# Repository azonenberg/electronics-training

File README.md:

Open source classes on electrical engineering and electronic hardware design

Each class is intended to be approximately a half day when offered consecutively in a conference/workshop format: 3
hours of lecture and 2 hour of lab.

# Current focus

* Oscilloscope probing, including detailed discussions of probe architectures and non-idealities

# Future ideas (may be more than one class each)

* Electronics merit badge
* EE 101
* PCB design
* High speed design
* EM simulation with Sonnet(?)

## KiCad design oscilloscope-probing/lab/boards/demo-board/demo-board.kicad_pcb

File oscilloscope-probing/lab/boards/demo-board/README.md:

# Demo board

## info

* ebay xc7a35t-2fgg484i
* stm32h750 running control plane
* 4x LVCMOS33 outputs for low speed stuff, wired direct from FPGA to SMAs
* A few GTPs to SMAs
* ltc3374a based power, usb-c, f234
* Some fast LVCMOS18 or similar outputs
* needs 32 mbit or larger spi flash, load more fw for stm32 from same flash if needed??

stackup: 8 layers SGS PG SGS JLC081611-2116?? going down to 6 probably wont save much

## BUGS BUGS BUGS in first board revision

* FT234 is 0.45mm pitch, footprint is 0.5. it should still solder, barely (150um max pin position error, 250um lands w/ 250um gaps)
* No pulldowns on rail enables, so they all turn on without sequencing until the supervisor is flashed and out of reset
* Not really a bug, but should have put DC blocks on PAM3 outputs so we don't need them scope side
* LTC3374A MODE pin is strapped low which causes high ripple on GTY VTT (1.2V) rail due to light load, should have been high
* Add lowpass filter to PAM3 outputs to simulate ethernet magnetics response
* Missing solder paste apertures on USB connector mechanical pins and several PTH headers that could otherwise have been pin-in-paste soldered

NOTE NOTE NOTE
Board 3 C122 has 10uf instead of 22

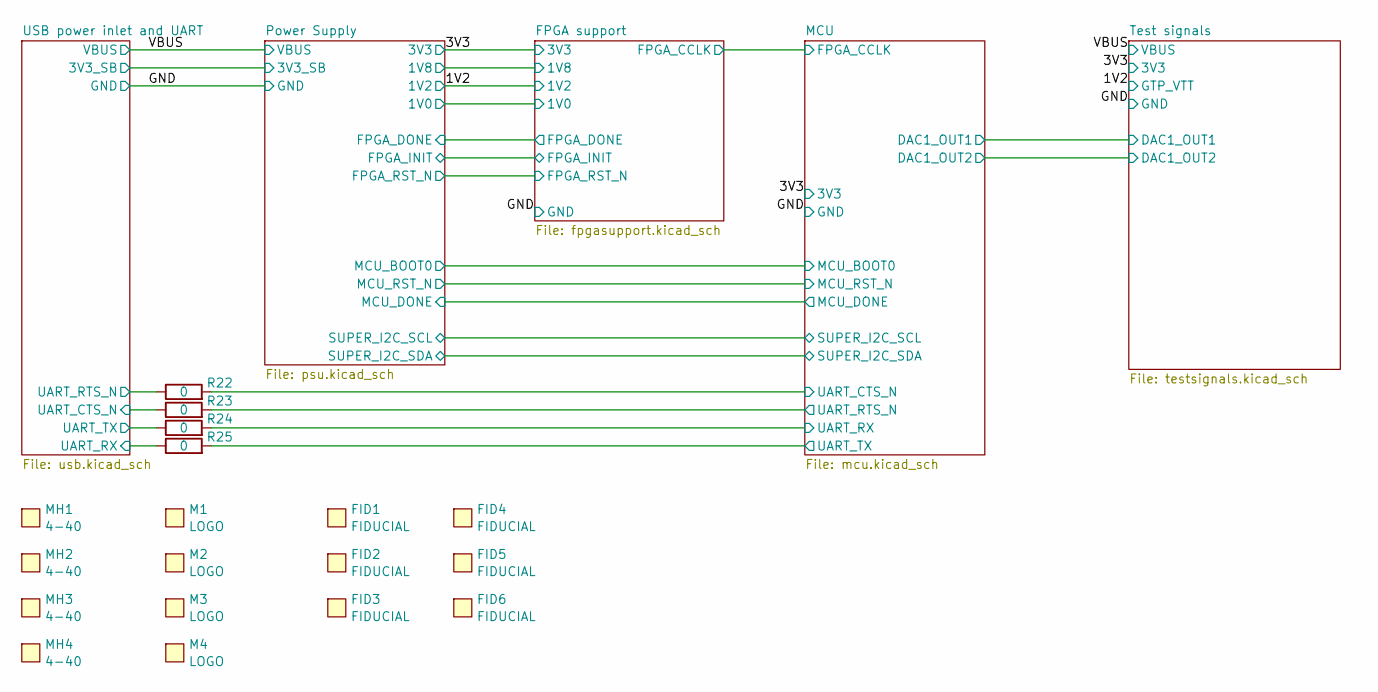
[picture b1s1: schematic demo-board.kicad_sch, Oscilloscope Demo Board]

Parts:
FID1, FID2, FID3, FID4, FID5, FID6: FIDUCIAL; FIDUCIAL_1MM
M1: LOGO; LONGTHING-1200DPI
M2: LOGO; Logo_silk_ROHS_5x2.8mm
M3: LOGO; Logo_silk_WEEE_3.4x5mm
M4: LOGO; Logo_silk_OSHW_6x6mm
MH1, MH2, MH3, MH4: 4-40; MECHANICAL_CLEARANCEHOLE_4_40
R22, R23, R24, R25: 0; EIA_0402_RES_NOSILK

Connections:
/MCU/UART_CTS_N: R22.2; also elsewhere on the board
/MCU/UART_RTS_N: R23.2; also elsewhere on the board
/MCU/UART_RX: R24.2; also elsewhere on the board
/MCU/UART_TX: R25.2; also elsewhere on the board
/USB power inlet and UART/UART_CTS_N: R23.1; also elsewhere on the board
/USB power inlet and UART/UART_RTS_N: R22.1; also elsewhere on the board
/USB power inlet and UART/UART_RX: R25.1; also elsewhere on the board
/USB power inlet and UART/UART_TX: R24.1; also elsewhere on the board

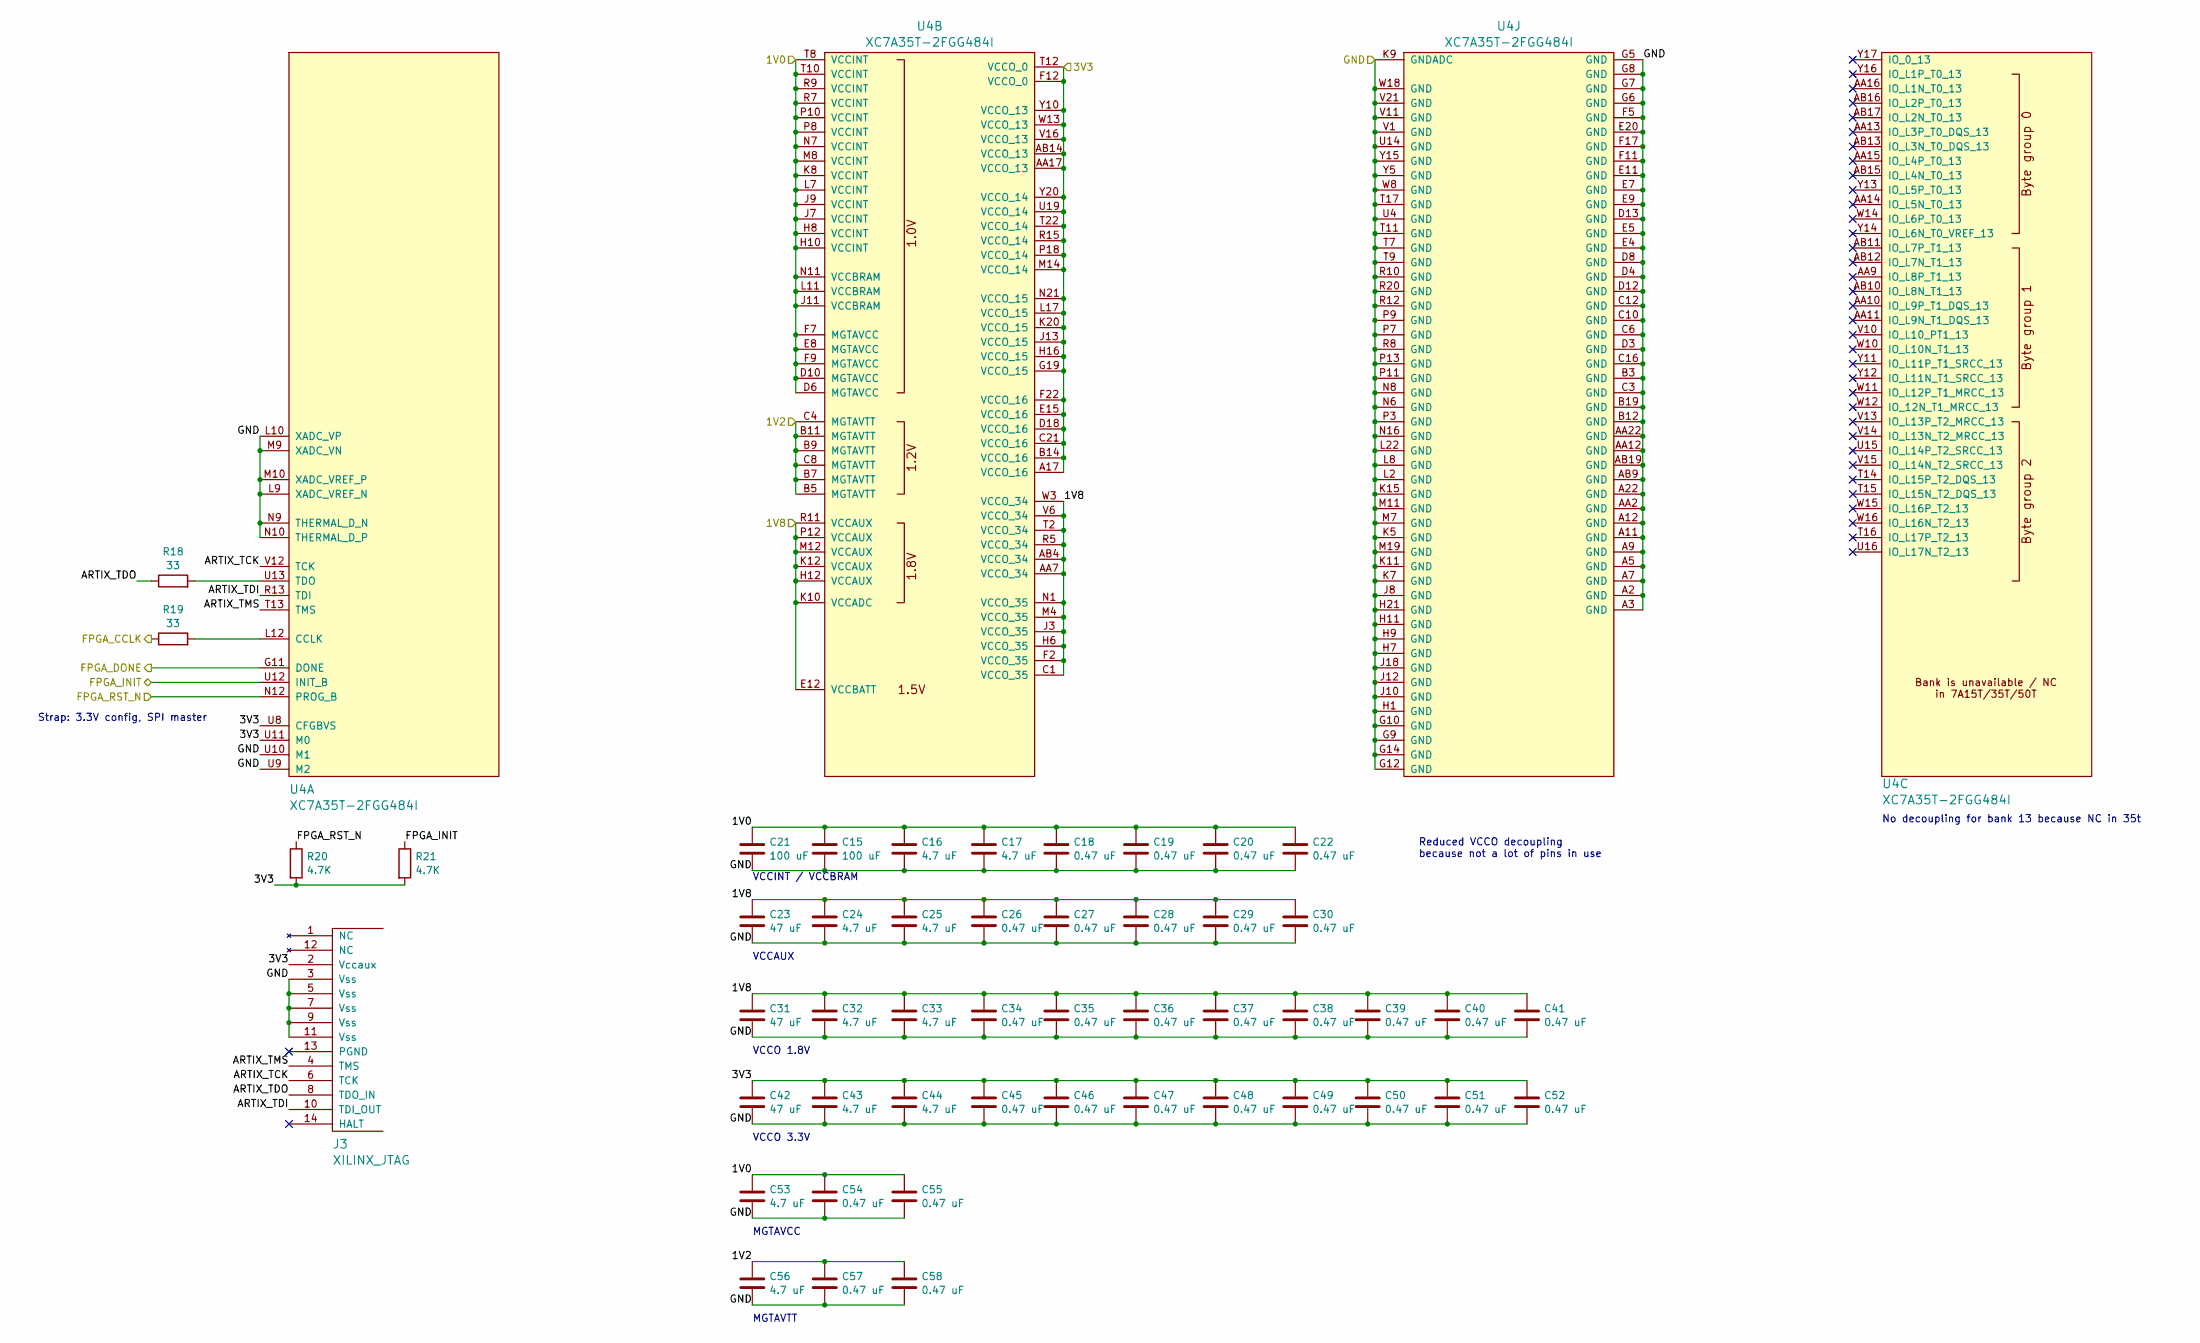
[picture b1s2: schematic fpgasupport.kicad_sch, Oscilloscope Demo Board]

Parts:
C15, C21: 100 uF; EIA_1206_CAP_NOSILK
C16, C17, C24, C25, C32, C33, C43, C44, C53, C56: 4.7 uF; EIA_0603_CAP_NOSILK
C18, C19, C20, C22, C26, C27, C28, C29, C30, C34, C35, C36, C37, C38, C39, C40, C41, C45, C46, C47, C48, C49, C50, C51, C52, C54, C55, C57, C58: 0.47 uF; EIA_0402_CAP_NOSILK
C23, C31, C42: 47 uF; EIA_1206_CAP_NOSILK
J3: XILINX_JTAG; XILINX_JTAG_PTH_MOLEX_0878311420
R18, R19: 33; EIA_0402_RES_NOSILK
R20, R21: 4.7K; EIA_0402_RES_NOSILK
U4: XC7A35T-2FGG484I; BGA_484_22x22_FULLARRAY_1MM

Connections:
/1V2: C56.1, C57.1, C58.1, U4.B5 (MGTAVTT), U4.B7 (MGTAVTT), U4.B9 (MGTAVTT), U4.B11 (MGTAVTT), U4.C4 (MGTAVTT), U4.C8 (MGTAVTT); also elsewhere on the board
/3V3: C42.1, C43.1, C44.1, C45.1, C46.1, C47.1, C48.1, C49.1, C50.1, C51.1, C52.1, J3.2 (Vccaux), R20.2, R21.2, U4.A17 (VCCO_16), U4.AA17 (VCCO_13), U4.AB14 (VCCO_13), U4.B14 (VCCO_16), U4.C21 (VCCO_16), U4.D18 (VCCO_16), U4.E15 (VCCO_16), U4.F12 (VCCO_0), U4.F22 (VCCO_16), U4.G19 (VCCO_15), U4.H16 (VCCO_15), U4.J13 (VCCO_15), U4.K20 (VCCO_15), U4.L17 (VCCO_15), U4.M14 (VCCO_14), U4.N21 (VCCO_15), U4.P18 (VCCO_14), U4.R15 (VCCO_14), U4.T12 (VCCO_0), U4.T22 (VCCO_14), U4.U8 (CFGBVS), U4.U11 (M0), U4.U19 (VCCO_14), U4.V16 (VCCO_13), U4.W13 (VCCO_13), U4.Y10 (VCCO_13), U4.Y20 (VCCO_14); also elsewhere on the board
/FPGA support/1V0: C15.1, C16.1, C17.1, C18.1, C19.1, C20.1, C21.1, C22.1, C53.1, C54.1, C55.1, U4.D6 (MGTAVCC), U4.D10 (MGTAVCC), U4.E8 (MGTAVCC), U4.F7 (MGTAVCC), U4.F9 (MGTAVCC), U4.H8 (VCCINT), U4.H10 (VCCINT), U4.J7 (VCCINT), U4.J9 (VCCINT), U4.J11 (VCCBRAM), U4.K8 (VCCINT), U4.L7 (VCCINT), U4.L11 (VCCBRAM), U4.M8 (VCCINT), U4.N7 (VCCINT), U4.N11 (VCCBRAM), U4.P8 (VCCINT), U4.P10 (VCCINT), U4.R7 (VCCINT), U4.R9 (VCCINT), U4.T8 (VCCINT), U4.T10 (VCCINT); also elsewhere on the board
/FPGA support/1V8: C23.1, C24.1, C25.1, C26.1, C27.1, C28.1, C29.1, C30.1, C31.1, C32.1, C33.1, C34.1, C35.1, C36.1, C37.1, C38.1, C39.1, C40.1, C41.1, U4.AA7 (VCCO_34), U4.AB4 (VCCO_34), U4.C1 (VCCO_35), U4.E12 (VCCBATT), U4.F2 (VCCO_35), U4.H6 (VCCO_35), U4.H12 (VCCAUX), U4.J3 (VCCO_35), U4.K10 (VCCADC), U4.K12 (VCCAUX), U4.M4 (VCCO_35), U4.M12 (VCCAUX), U4.N1 (VCCO_35), U4.P12 (VCCAUX), U4.R5 (VCCO_34), U4.R11 (VCCAUX), U4.T2 (VCCO_34), U4.V6 (VCCO_34), U4.W3 (VCCO_34); also elsewhere on the board
/FPGA support/ARTIX_TCK: J3.6 (TCK), U4.V12 (TCK)
/FPGA support/ARTIX_TDI: J3.10 (TDI_OUT), U4.R13 (TDI)
/FPGA support/ARTIX_TDO: J3.8 (TDO_IN), R18.1
/FPGA support/ARTIX_TMS: J3.4 (TMS), U4.T13 (TMS)
/FPGA support/FPGA_CCLK: R19.1; also elsewhere on the board
/FPGA support/FPGA_DONE: U4.G11 (DONE); also elsewhere on the board
/FPGA support/FPGA_INIT: R21.1, U4.U12 (INIT_B); also elsewhere on the board
/FPGA support/FPGA_RST_N: R20.1, U4.N12 (PROG_B); also elsewhere on the board
/GND: C15.2, C16.2, C17.2, C18.2, C19.2, C20.2, C21.2, C22.2, C23.2, C24.2, C25.2, C26.2, C27.2, C28.2, C29.2, C30.2, C31.2, C32.2, C33.2, C34.2, C35.2, C36.2, C37.2, C38.2, C39.2, C40.2, C41.2, C42.2, C43.2, C44.2, C45.2, C46.2, C47.2, C48.2, C49.2, C50.2, C51.2, C52.2, C53.2, C54.2, C55.2, C56.2, C57.2, C58.2, J3.3 (Vss), J3.5 (Vss), J3.7 (Vss), J3.9 (Vss), J3.11 (Vss), U4.A2 (GND), U4.A3 (GND), U4.A5 (GND), U4.A7 (GND), U4.A9 (GND), U4.A11 (GND), U4.A12 (GND), U4.A22 (GND), U4.AA2 (GND), U4.AA12 (GND), U4.AA22 (GND), U4.AB9 (GND), U4.AB19 (GND), U4.B3 (GND), U4.B12 (GND), U4.B19 (GND), U4.C3 (GND), U4.C6 (GND), U4.C10 (GND), U4.C12 (GND), U4.C16 (GND), U4.D3 (GND), U4.D4 (GND), U4.D8 (GND), U4.D12 (GND), U4.D13 (GND), U4.E4 (GND), U4.E5 (GND), U4.E7 (GND), U4.E9 (GND), U4.E11 (GND), U4.E20 (GND), U4.F5 (GND), U4.F11 (GND), U4.F17 (GND), U4.G5 (GND), U4.G6 (GND), U4.G7 (GND), U4.G8 (GND), U4.G9 (GND), U4.G10 (GND), U4.G12 (GND), U4.G14 (GND), U4.H1 (GND), U4.H7 (GND), U4.H9 (GND), U4.H11 (GND), U4.H21 (GND), U4.J8 (GND), U4.J10 (GND), U4.J12 (GND), U4.J18 (GND), U4.K5 (GND), U4.K7 (GND), U4.K9 (GNDADC), U4.K11 (GND), U4.K15 (GND), U4.L2 (GND), U4.L8 (GND), U4.L9 (XADC_VREF_N), U4.L10 (XADC_VP), U4.L22 (GND), U4.M7 (GND), U4.M9 (XADC_VN), U4.M10 (XADC_VREF_P), U4.M11 (GND), U4.M19 (GND), U4.N6 (GND), U4.N8 (GND), U4.N9 (THERMAL_D_N), U4.N10 (THERMAL_D_P), U4.N16 (GND), U4.P3 (GND), U4.P7 (GND), U4.P9 (GND), U4.P11 (GND), U4.P13 (GND), U4.R8 (GND), U4.R10 (GND), U4.R12 (GND), U4.R20 (GND), U4.T7 (GND), U4.T9 (GND), U4.T11 (GND), U4.T17 (GND), U4.U4 (GND), U4.U9 (M2), U4.U10 (M1), U4.U14 (GND), U4.V1 (GND), U4.V11 (GND), U4.V21 (GND), U4.W8 (GND), U4.W18 (GND), U4.Y5 (GND), U4.Y15 (GND); also elsewhere on the board
unnamed: R19.2, U4.L12 (CCLK)
unnamed: R18.2, U4.U13 (TDO)

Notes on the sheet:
VCCO 1.8V
VCCINT / VCCBRAM
MGTAVCC
Reduced VCCO decoupling because not a lot of pins in use
Strap: 3.3V config, SPI master
MGTAVTT
No decoupling for bank 13 because NC in 35t
VCCAUX
VCCO 3.3V

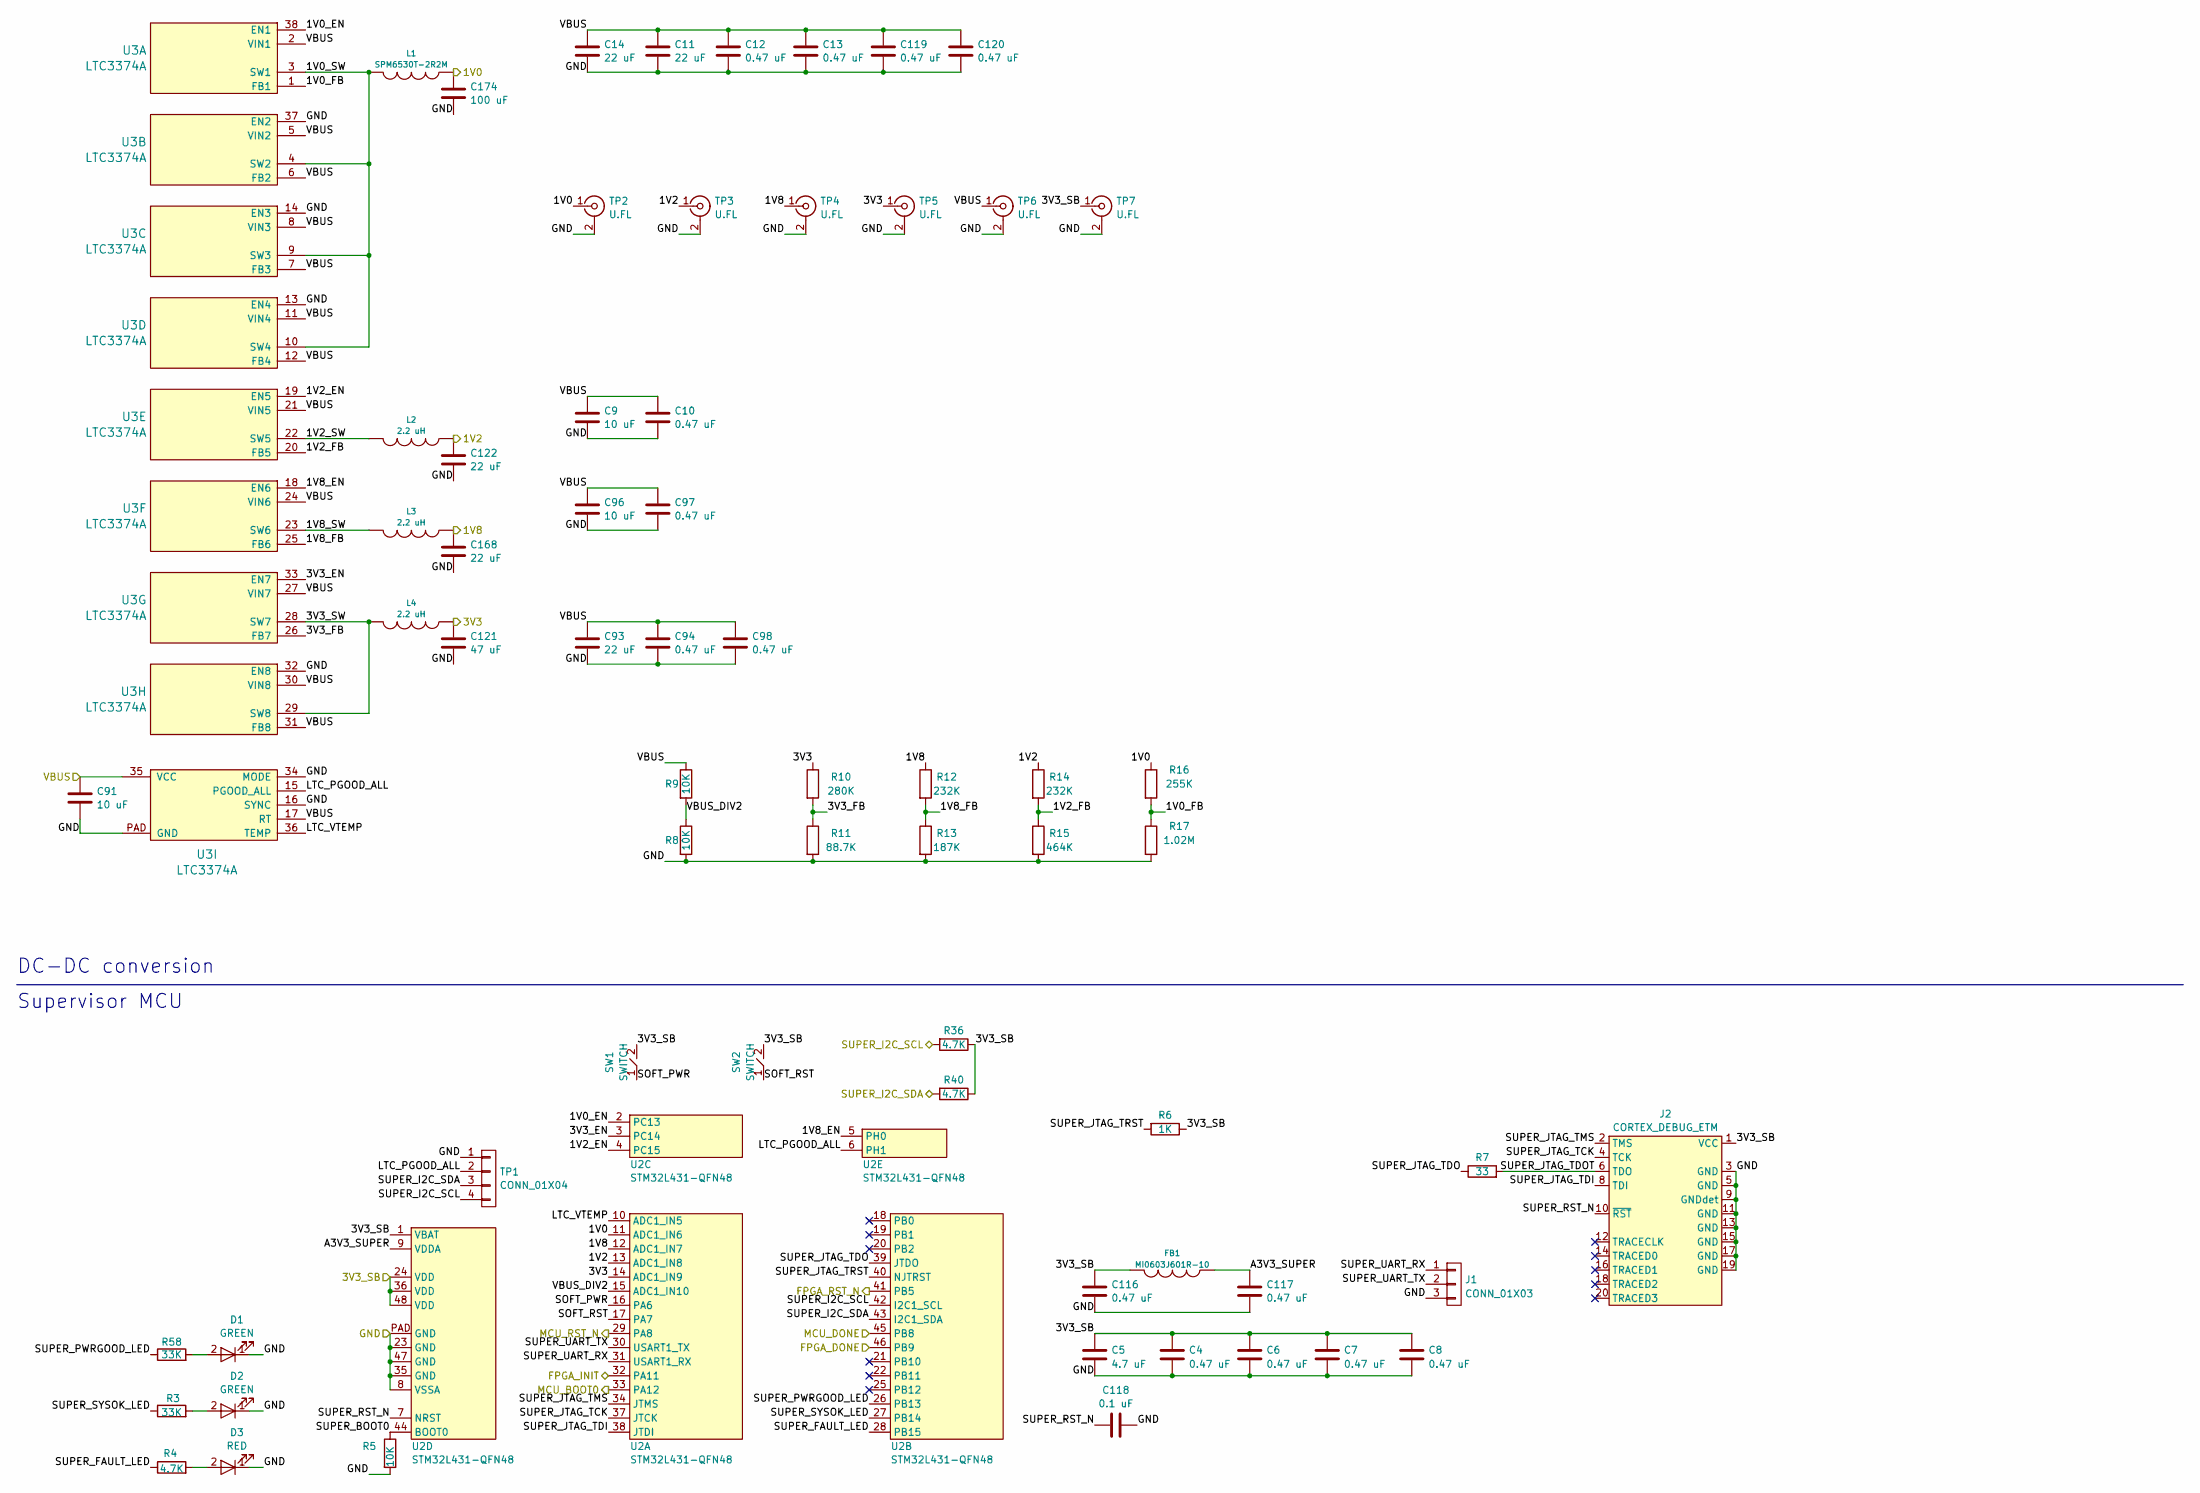
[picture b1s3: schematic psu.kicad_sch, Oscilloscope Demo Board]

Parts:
C4, C6, C7, C8, C10, C12, C13, C94, C97, C98, C116, C117, C119, C120: 0.47 uF; EIA_0402_CAP_NOSILK
C5: 4.7 uF; EIA_0603_CAP_NOSILK
C9, C91, C96: 10 uF; EIA_1210_CAP_NOSILK
C11, C14, C93: 22 uF; EIA_1210_CAP_NOSILK
C118: 0.1 uF; EIA_0402_CAP_NOSILK
C121: 47 uF; EIA_1210_CAP_NOSILK
C122, C168: 22 uF; EIA_0805_CAP_NOSILK
C174: 100 uF; EIA_1210_CAP_NOSILK
D1, D2: GREEN; EIA_0402_LED
D3: RED; EIA_0402_LED
FB1: MI0603J601R-10; EIA_0603_INDUCTOR_NOSILK
J1: CONN_01X03; CONN_HEADER_2.54MM_1x3
J2: CORTEX_DEBUG_ETM; CONN_HEADER_1.27MM_2x10_SMT_SAMTEC_FTSH-110-01-L-DV-K
L1: SPM6530T-2R2M; INDUCTOR_TDK_SPM6530
L2, L3, L4: 2.2 uH; EIA_1210_CAP_NOSILK
R3, R58: 33K; EIA_0402_RES_NOSILK
R4, R36, R40: 4.7K; EIA_0402_RES_NOSILK
R5, R8, R9: 10K; EIA_0402_RES_NOSILK
R6: 1K; EIA_0402_RES_NOSILK
R7: 33; EIA_0402_RES_NOSILK
R10: 280K; EIA_0402_RES_NOSILK
R11: 88.7K; EIA_0402_RES_NOSILK
R12, R14: 232K; EIA_0402_RES_NOSILK
R13: 187K; EIA_0402_RES_NOSILK
R15: 464K; EIA_0402_RES_NOSILK
R16: 255K; EIA_0402_RES_NOSILK
R17: 1.02M; EIA_0402_RES_NOSILK
SW1, SW2: SWITCH; SWITCH_RAFI_MICON_5
TP1: CONN_01X04; CONN_HEADER_2.54MM_1x4
TP2, TP3, TP4, TP5, TP6, TP7: U.FL; CONN_U.FL_TE_1909763-1
U2: STM32L431-QFN48; QFN_48_0.5MM_7x7MM
U3: LTC3374A; QFN_38_0.5MM_5x7MM

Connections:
/1V2: C122.1, L2.1, R14.1, TP3.1 (In), U2.13 (ADC1_IN8); also elsewhere on the board
/3V3: C121.1, L4.1, R10.1, TP5.1 (In), U2.14 (ADC1_IN9); also elsewhere on the board
/FPGA support/1V0: C174.1, L1.1, R16.1, TP2.1 (In), U2.11 (ADC1_IN6); also elsewhere on the board
/FPGA support/1V8: C168.1, L3.1, R12.1, TP4.1 (In), U2.12 (ADC1_IN7); also elsewhere on the board
/FPGA support/FPGA_DONE: U2.46 (PB9); also elsewhere on the board
/FPGA support/FPGA_INIT: U2.32 (PA11); also elsewhere on the board
/FPGA support/FPGA_RST_N: U2.41 (PB5); also elsewhere on the board
/GND: C4.2, C5.2, C6.2, C7.2, C8.2, C9.2, C10.2, C11.2, C12.2, C13.2, C14.2, C91.2, C93.2, C94.2, C96.2, C97.2, C98.2, C116.2, C117.2, C118.2, C119.2, C120.2, C121.2, C122.2, C168.2, C174.2, D1.1 (K), D2.1 (K), D3.1 (K), J1.3, J2.3 (GND), J2.5 (GND), J2.9 (GNDdet), J2.11 (GND), J2.13 (GND), J2.15 (GND), J2.17 (GND), J2.19 (GND), R5.2, R8.2, R11.2, R13.2, R15.2, R17.2, TP1.1, TP2.2 (Ext), TP3.2 (Ext), TP4.2 (Ext), TP5.2 (Ext), TP6.2 (Ext), TP7.2 (Ext), U2.8 (VSSA), U2.23 (GND), U2.35 (GND), U2.47 (GND), U2.PAD (GND), U3.13 (EN4), U3.14 (EN3), U3.16 (SYNC), U3.32 (EN8), U3.34 (MODE), U3.37 (EN2), U3.PAD (GND); also elsewhere on the board
/MCU/MCU_BOOT0: U2.33 (PA12); also elsewhere on the board
/MCU/MCU_DONE: U2.45 (PB8); also elsewhere on the board
/MCU/MCU_RST_N: U2.29 (PA8); also elsewhere on the board
/Power Supply/1V0_EN: U2.2 (PC13), U3.38 (EN1)
/Power Supply/1V0_FB: R16.2, R17.1, U3.1 (FB1)
/Power Supply/1V0_SW: L1.2, U3.3 (SW1), U3.4 (SW2), U3.9 (SW3), U3.10 (SW4)
/Power Supply/1V2_EN: U2.4 (PC15), U3.19 (EN5)
/Power Supply/1V2_FB: R14.2, R15.1, U3.20 (FB5)
/Power Supply/1V2_SW: L2.2, U3.22 (SW5)
/Power Supply/1V8_EN: U2.5 (PH0), U3.18 (EN6)
/Power Supply/1V8_FB: R12.2, R13.1, U3.25 (FB6)
/Power Supply/1V8_SW: L3.2, U3.23 (SW6)
/Power Supply/3V3_EN: U2.3 (PC14), U3.33 (EN7)
/Power Supply/3V3_FB: R10.2, R11.1, U3.26 (FB7)
/Power Supply/3V3_SB: C4.1, C5.1, C6.1, C7.1, C8.1, C116.1, FB1.2, J2.1 (VCC), R6.1, R36.1, R40.1, SW1.2, SW2.2, TP7.1 (In), U2.1 (VBAT), U2.24 (VDD), U2.36 (VDD), U2.48 (VDD); also elsewhere on the board
/Power Supply/3V3_SW: L4.2, U3.28 (SW7), U3.29 (SW8)
/Power Supply/A3V3_SUPER: C117.1, FB1.1, U2.9 (VDDA)
/Power Supply/LTC_PGOOD_ALL: TP1.2, U2.6 (PH1), U3.15 (PGOOD_ALL)
/Power Supply/LTC_VTEMP: U2.10 (ADC1_IN5), U3.36 (TEMP)
/Power Supply/SOFT_PWR: SW1.1, U2.16 (PA6)
/Power Supply/SOFT_RST: SW2.1, U2.17 (PA7)
/Power Supply/SUPER_BOOT0: R5.1, U2.44 (BOOT0)
/Power Supply/SUPER_FAULT_LED: R4.1, U2.28 (PB15)
/Power Supply/SUPER_I2C_SCL: R36.2, TP1.4, U2.42 (I2C1_SCL); also elsewhere on the board
/Power Supply/SUPER_I2C_SDA: R40.2, TP1.3, U2.43 (I2C1_SDA); also elsewhere on the board
/Power Supply/SUPER_JTAG_TCK: J2.4 (TCK), U2.37 (JTCK)
/Power Supply/SUPER_JTAG_TDI: J2.8 (TDI), U2.38 (JTDI)
/Power Supply/SUPER_JTAG_TDO: R7.1, U2.39 (JTDO)
/Power Supply/SUPER_JTAG_TDOT: J2.6 (TDO), R7.2
/Power Supply/SUPER_JTAG_TMS: J2.2 (TMS), U2.34 (JTMS)
/Power Supply/SUPER_JTAG_TRST: R6.2, U2.40 (NJTRST)
/Power Supply/SUPER_PWRGOOD_LED: R58.1, U2.26 (PB13)
/Power Supply/SUPER_RST_N: C118.1, J2.10 (~RST), U2.7 (NRST)
/Power Supply/SUPER_SYSOK_LED: R3.1, U2.27 (PB14)
/Power Supply/SUPER_UART_RX: J1.1, U2.31 (USART1_RX)
/Power Supply/SUPER_UART_TX: J1.2, U2.30 (USART1_TX)
/Power Supply/VBUS_DIV2: R8.1, R9.2, U2.15 (ADC1_IN10)
/VBUS: C9.1, C10.1, C11.1, C12.1, C13.1, C14.1, C91.1, C93.1, C94.1, C96.1, C97.1, C98.1, C119.1, C120.1, R9.1, TP6.1 (In), U3.2 (VIN1), U3.5 (VIN2), U3.6 (FB2), U3.7 (FB3), U3.8 (VIN3), U3.11 (VIN4), U3.12 (FB4), U3.17 (RT), U3.21 (VIN5), U3.24 (VIN6), U3.27 (VIN7), U3.30 (VIN8), U3.31 (FB8), U3.35 (VCC); also elsewhere on the board
unnamed: D1.2 (A), R58.2
unnamed: D2.2 (A), R3.2
unnamed: D3.2 (A), R4.2

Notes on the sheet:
DC-DC conversion
Supervisor MCU

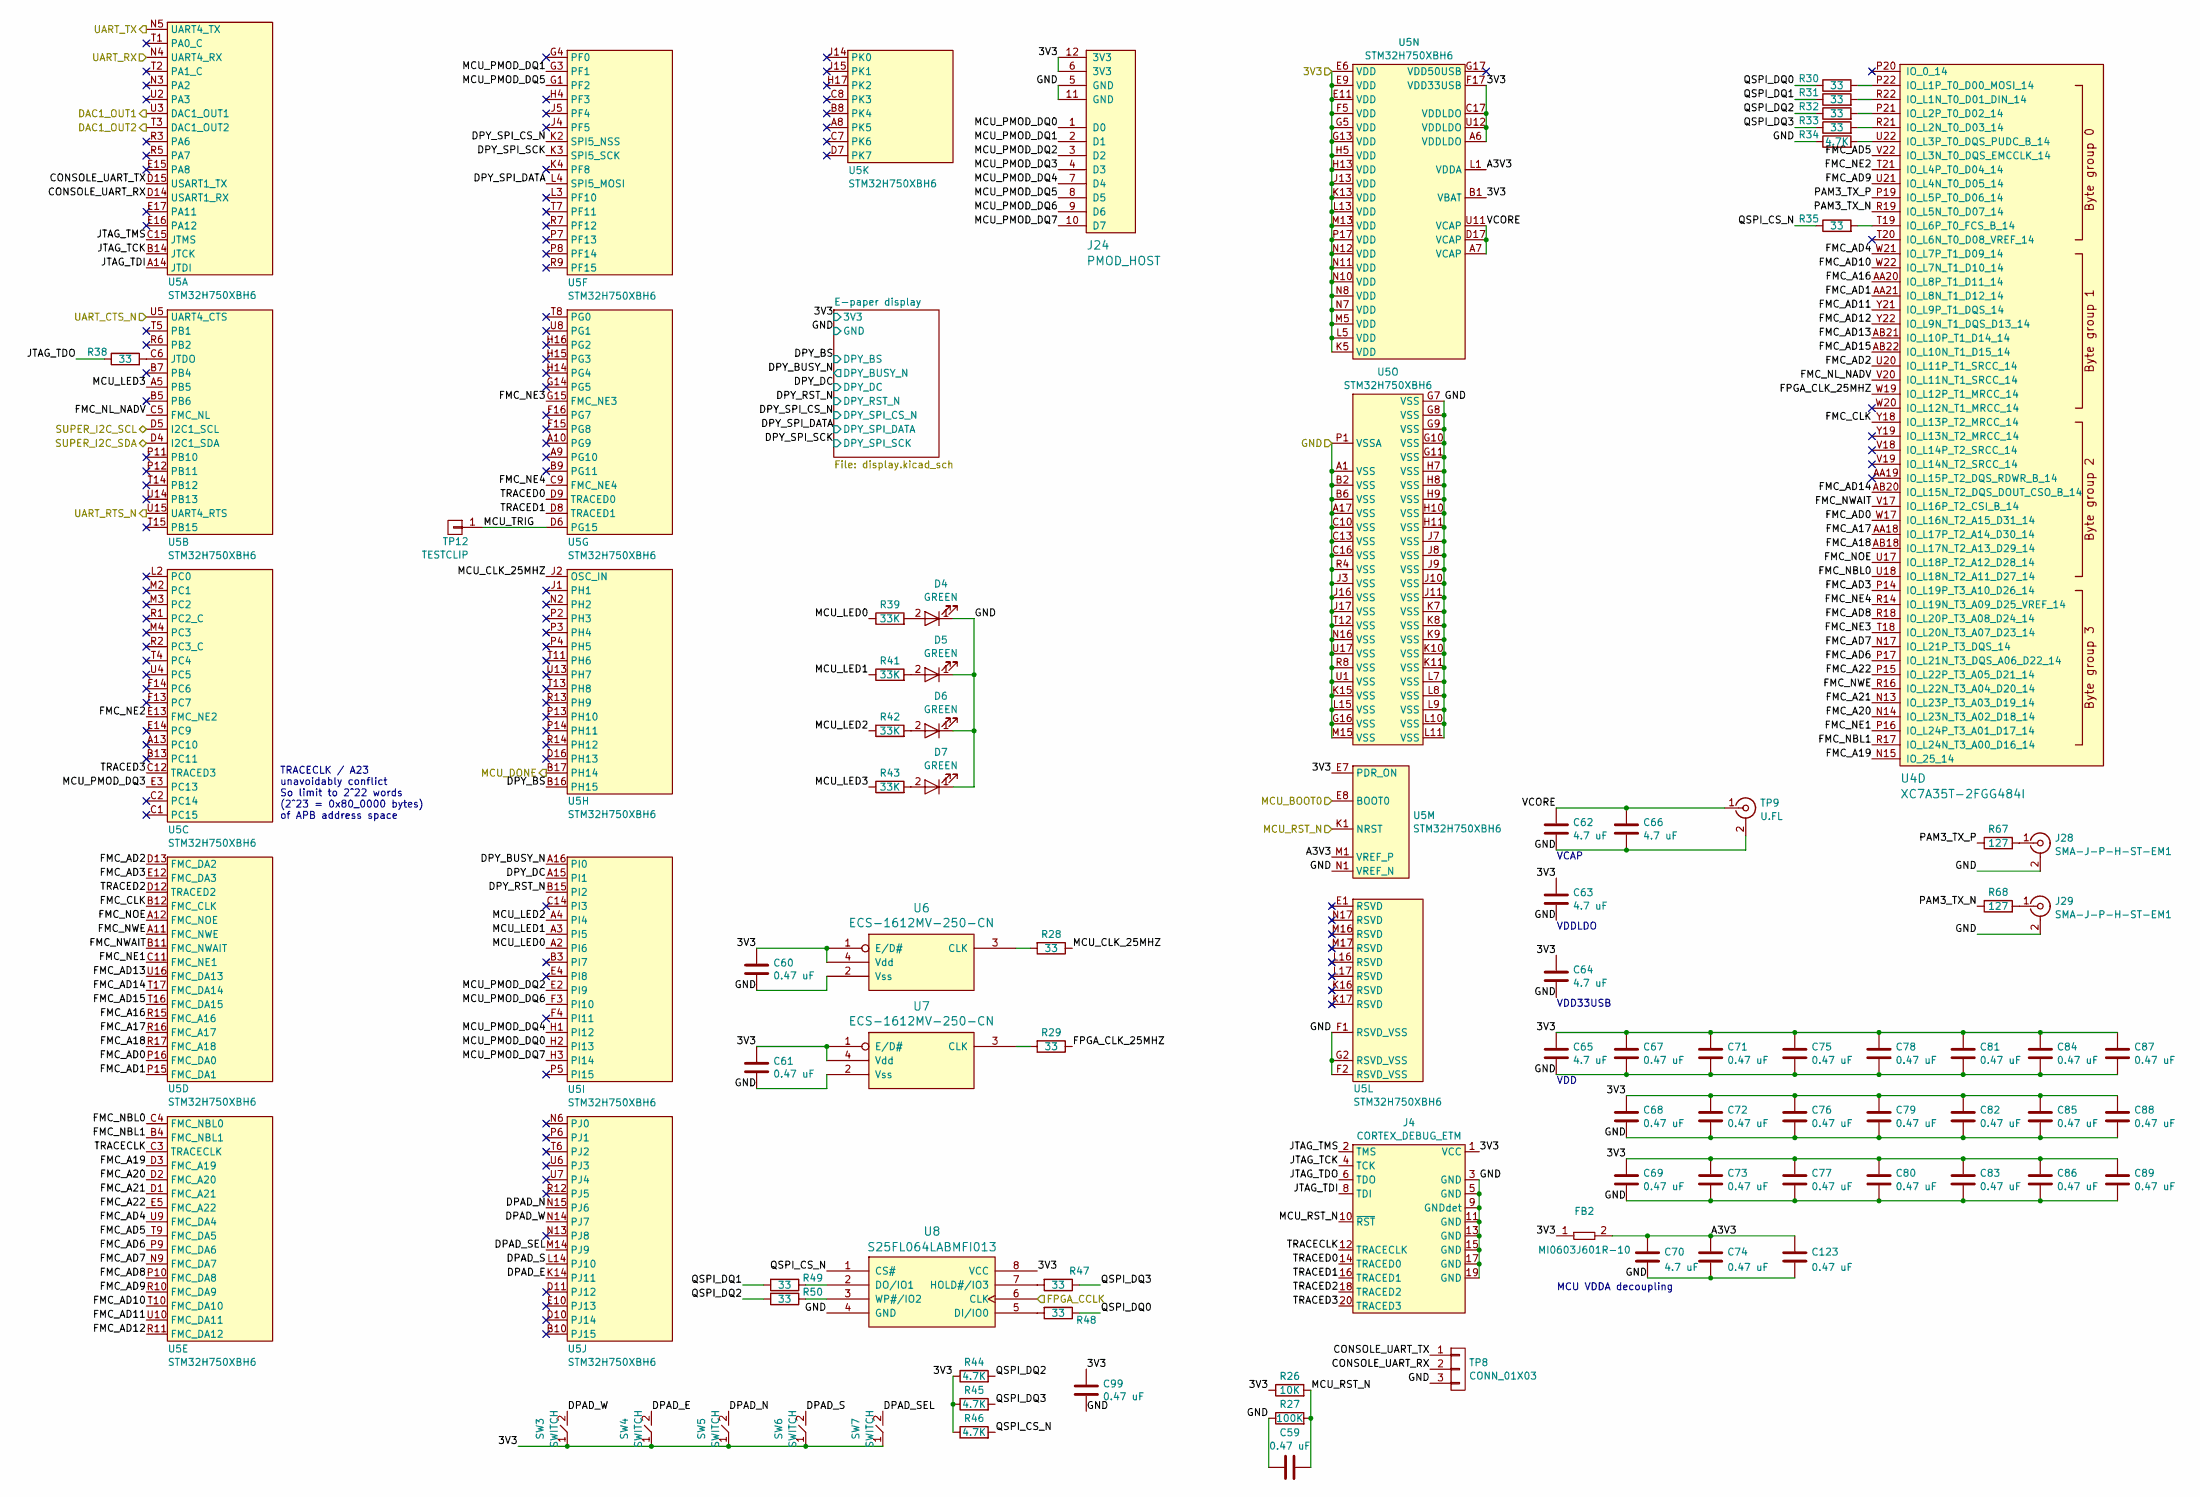
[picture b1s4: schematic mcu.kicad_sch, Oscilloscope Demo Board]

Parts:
C59, C60, C61, C67, C68, C69, C71, C72, C73, C74, C75, C76, C77, C78, C79, C80, C81, C82, C83, C84, C85, C86, C87, C88, C89, C99, C123: 0.47 uF; EIA_0402_CAP_NOSILK
C62, C63, C64, C65, C66, C70: 4.7 uF; EIA_0603_CAP_NOSILK
D4, D5, D6, D7: GREEN; EIA_0402_LED
FB2: MI0603J601R-10; EIA_0603_INDUCTOR_NOSILK
J4: CORTEX_DEBUG_ETM; CONN_HEADER_1.27MM_2x10_SMT_SAMTEC_FTSH-110-01-L-DV-K
J24: PMOD_HOST; CONN_HEADER_2.54MM_2x6_RA_PMOD_HOST
J28, J29: SMA-J-P-H-ST-EM1; CONN_SMA_EDGE_SAMTEC_SMA_J_P_H_ST_EM1_NOPASTE
R26: 10K; EIA_0402_RES_NOSILK
R27: 100K; EIA_0402_RES_NOSILK
R28, R29, R30, R31, R32, R33, R35, R38, R47, R48, R49, R50: 33; EIA_0402_RES_NOSILK
R34, R44, R45, R46: 4.7K; EIA_0402_RES_NOSILK
R39, R41, R42, R43: 33K; EIA_0402_RES_NOSILK
R67, R68: 127; EIA_0402_RES_NOSILK
SW3, SW4, SW5, SW6, SW7: SWITCH; SWITCH_RAFI_MICON_5
TP8: CONN_01X03; CONN_HEADER_2.54MM_1x3_REFLOW
TP9: U.FL; CONN_U.FL_TE_1909763-1
TP12: TESTCLIP; TESTPOINT_SMT_KEYSTONE_5016
U4: XC7A35T-2FGG484I; BGA_484_22x22_FULLARRAY_1MM
U5: STM32H750XBH6; BGA_265_14x14_DEPOP_0.8MM
U6, U7: ECS-1612MV-250-CN; OSCILLATOR_1.6x1.2
U8: S25FL064LABMFI013; SOIC_8_5.3MM

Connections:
/3V3: C60.1, C61.1, C63.1, C64.1, C65.1, C67.1, C68.1, C69.1, C71.1, C72.1, C73.1, C75.1, C76.1, C77.1, C78.1, C79.1, C80.1, C81.1, C82.1, C83.1, C84.1, C85.1, C86.1, C87.1, C88.1, C89.1, C99.1, FB2.1, J4.1 (VCC), J24.6 (3V3), J24.12 (3V3), R26.1, R44.1, R45.1, R46.1, SW3.1, SW4.1, SW5.1, SW6.1, SW7.1, U5.A6 (VDDLDO), U5.B1 (VBAT), U5.C17 (VDDLDO), U5.E6 (VDD), U5.E7 (PDR_ON), U5.E9 (VDD), U5.E11 (VDD), U5.F5 (VDD), U5.F17 (VDD33USB), U5.G5 (VDD), U5.G13 (VDD), U5.H5 (VDD), U5.H13 (VDD), U5.J13 (VDD), U5.K5 (VDD), U5.K13 (VDD), U5.L5 (VDD), U5.L13 (VDD), U5.M5 (VDD), U5.M13 (VDD), U5.N7 (VDD), U5.N8 (VDD), U5.N10 (VDD), U5.N11 (VDD), U5.N12 (VDD), U5.P17 (VDD), U5.U12 (VDDLDO), U6.1 (E/D#), U6.4 (Vdd), U7.1 (E/D#), U7.4 (Vdd), U8.8 (VCC); also elsewhere on the board
/FPGA support/FPGA_CCLK: U8.6 (CLK); also elsewhere on the board
/GND: C59.1, C60.2, C61.2, C62.2, C63.2, C64.2, C65.2, C66.2, C67.2, C68.2, C69.2, C70.2, C71.2, C72.2, C73.2, C74.2, C75.2, C76.2, C77.2, C78.2, C79.2, C80.2, C81.2, C82.2, C83.2, C84.2, C85.2, C86.2, C87.2, C88.2, C89.2, C99.2, C123.2, D4.1 (K), D5.1 (K), D6.1 (K), D7.1 (K), J4.3 (GND), J4.5 (GND), J4.9 (GNDdet), J4.11 (GND), J4.13 (GND), J4.15 (GND), J4.17 (GND), J4.19 (GND), J24.5 (GND), J24.11 (GND), J28.2 (Ext), J29.2 (Ext), R27.1, R34.1, TP8.3, TP9.2 (Ext), U5.A1 (VSS), U5.A17 (VSS), U5.B2 (VSS), U5.B6 (VSS), U5.C10 (VSS), U5.C13 (VSS), U5.C16 (VSS), U5.F1 (RSVD_VSS), U5.F2 (RSVD_VSS), U5.G2 (RSVD_VSS), U5.G7 (VSS), U5.G8 (VSS), U5.G9 (VSS), U5.G10 (VSS), U5.G11 (VSS), U5.G16 (VSS), U5.H7 (VSS), U5.H8 (VSS), U5.H9 (VSS), U5.H10 (VSS), U5.H11 (VSS), U5.J3 (VSS), U5.J7 (VSS), U5.J8 (VSS), U5.J9 (VSS), U5.J10 (VSS), U5.J11 (VSS), U5.J16 (VSS), U5.J17 (VSS), U5.K7 (VSS), U5.K8 (VSS), U5.K9 (VSS), U5.K10 (VSS), U5.K11 (VSS), U5.K15 (VSS), U5.L7 (VSS), U5.L8 (VSS), U5.L9 (VSS), U5.L10 (VSS), U5.L11 (VSS), U5.L15 (VSS), U5.M15 (VSS), U5.N1 (VREF_N), U5.N16 (VSS), U5.P1 (VSSA), U5.R4 (VSS), U5.R8 (VSS), U5.T12 (VSS), U5.U1 (VSS), U5.U17 (VSS), U6.2 (Vss), U7.2 (Vss), U8.4 (GND); also elsewhere on the board
/MCU/A3V3: C70.1, C74.1, C123.1, FB2.2, U5.L1 (VDDA), U5.M1 (VREF_P)
/MCU/CONSOLE_UART_RX: TP8.2, U5.D14 (USART1_RX)
/MCU/CONSOLE_UART_TX: TP8.1, U5.D15 (USART1_TX)
/MCU/DAC1_OUT1: U5.U3 (DAC1_OUT1); also elsewhere on the board
/MCU/DAC1_OUT2: U5.T3 (DAC1_OUT2); also elsewhere on the board
/MCU/DPAD_E: SW4.2, U5.K14 (PJ11)
/MCU/DPAD_N: SW5.2, U5.N15 (PJ6)
/MCU/DPAD_S: SW6.2, U5.L14 (PJ10)
/MCU/DPAD_SEL: SW7.2, U5.M14 (PJ9)
/MCU/DPAD_W: SW3.2, U5.N14 (PJ7)
/MCU/DPY_BS: U5.B16 (PH15); also elsewhere on the board
/MCU/DPY_BUSY_N: U5.A16 (PI0); also elsewhere on the board
/MCU/DPY_DC: U5.A15 (PI1); also elsewhere on the board
/MCU/DPY_RST_N: U5.B15 (PI2); also elsewhere on the board
/MCU/DPY_SPI_CS_N: U5.K2 (SPI5_NSS); also elsewhere on the board
/MCU/DPY_SPI_DATA: U5.L4 (SPI5_MOSI); also elsewhere on the board
/MCU/DPY_SPI_SCK: U5.K3 (SPI5_SCK); also elsewhere on the board
/MCU/FMC_A16: U4.AA20 (IO_L8P_T1_D11_14), U5.R15 (FMC_A16)
/MCU/FMC_A17: U4.AA18 (IO_L17P_T2_A14_D30_14), U5.R16 (FMC_A17)
/MCU/FMC_A18: U4.AB18 (IO_L17N_T2_A13_D29_14), U5.R17 (FMC_A18)
/MCU/FMC_A19: U4.N15 (IO_25_14), U5.D3 (FMC_A19)
/MCU/FMC_A20: U4.N14 (IO_L23N_T3_A02_D18_14), U5.D2 (FMC_A20)
/MCU/FMC_A21: U4.N13 (IO_L23P_T3_A03_D19_14), U5.D1 (FMC_A21)
/MCU/FMC_A22: U4.P15 (IO_L22P_T3_A05_D21_14), U5.E5 (FMC_A22)
/MCU/FMC_AD0: U4.W17 (IO_L16N_T2_A15_D31_14), U5.P16 (FMC_DA0)
/MCU/FMC_AD1: U4.AA21 (IO_L8N_T1_D12_14), U5.P15 (FMC_DA1)
/MCU/FMC_AD2: U4.U20 (IO_L11P_T1_SRCC_14), U5.D13 (FMC_DA2)
/MCU/FMC_AD3: U4.P14 (IO_L19P_T3_A10_D26_14), U5.E12 (FMC_DA3)
/MCU/FMC_AD4: U4.W21 (IO_L7P_T1_D09_14), U5.U9 (FMC_DA4)
/MCU/FMC_AD5: U4.V22 (IO_L3N_T0_DQS_EMCCLK_14), U5.T9 (FMC_DA5)
/MCU/FMC_AD6: U4.P17 (IO_L21N_T3_DQS_A06_D22_14), U5.P9 (FMC_DA6)
/MCU/FMC_AD7: U4.N17 (IO_L21P_T3_DQS_14), U5.N9 (FMC_DA7)
/MCU/FMC_AD8: U4.R18 (IO_L20P_T3_A08_D24_14), U5.P10 (FMC_DA8)
/MCU/FMC_AD9: U4.U21 (IO_L4N_T0_D05_14), U5.R10 (FMC_DA9)
/MCU/FMC_AD10: U4.W22 (IO_L7N_T1_D10_14), U5.T10 (FMC_DA10)
/MCU/FMC_AD11: U4.Y21 (IO_L9P_T1_DQS_14), U5.U10 (FMC_DA11)
/MCU/FMC_AD12: U4.Y22 (IO_L9N_T1_DQS_D13_14), U5.R11 (FMC_DA12)
/MCU/FMC_AD13: U4.AB21 (IO_L10P_T1_D14_14), U5.U16 (FMC_DA13)
/MCU/FMC_AD14: U4.AB20 (IO_L15N_T2_DQS_DOUT_CSO_B_14), U5.T17 (FMC_DA14)
/MCU/FMC_AD15: U4.AB22 (IO_L10N_T1_D15_14), U5.T16 (FMC_DA15)
/MCU/FMC_CLK: U4.Y18 (IO_L13P_T2_MRCC_14), U5.B12 (FMC_CLK)
/MCU/FMC_NBL0: U4.U18 (IO_L18N_T2_A11_D27_14), U5.C4 (FMC_NBL0)
/MCU/FMC_NBL1: U4.R17 (IO_L24N_T3_A00_D16_14), U5.B4 (FMC_NBL1)
/MCU/FMC_NE1: U4.P16 (IO_L24P_T3_A01_D17_14), U5.C11 (FMC_NE1)
/MCU/FMC_NE2: U4.T21 (IO_L4P_T0_D04_14), U5.E13 (FMC_NE2)
/MCU/FMC_NE3: U4.T18 (IO_L20N_T3_A07_D23_14), U5.G15 (FMC_NE3)
/MCU/FMC_NE4: U4.R14 (IO_L19N_T3_A09_D25_VREF_14), U5.C9 (FMC_NE4)
/MCU/FMC_NL_NADV: U4.V20 (IO_L11N_T1_SRCC_14), U5.C5 (FMC_NL)
/MCU/FMC_NOE: U4.U17 (IO_L18P_T2_A12_D28_14), U5.A12 (FMC_NOE)
/MCU/FMC_NWAIT: U4.V17 (IO_L16P_T2_CSI_B_14), U5.B11 (FMC_NWAIT)
/MCU/FMC_NWE: U4.R16 (IO_L22N_T3_A04_D20_14), U5.A11 (FMC_NWE)
/MCU/FPGA_CLK_25MHZ: R29.1, U4.W19 (IO_L12P_T1_MRCC_14)
/MCU/JTAG_TCK: J4.4 (TCK), U5.B14 (JTCK)
/MCU/JTAG_TDI: J4.8 (TDI), U5.A14 (JTDI)
/MCU/JTAG_TDO: J4.6 (TDO), R38.1
/MCU/JTAG_TMS: J4.2 (TMS), U5.C15 (JTMS)
/MCU/MCU_BOOT0: U5.E8 (BOOT0); also elsewhere on the board
/MCU/MCU_CLK_25MHZ: R28.1, U5.J2 (OSC_IN)
/MCU/MCU_DONE: U5.B17 (PH14); also elsewhere on the board
/MCU/MCU_LED0: R39.1, U5.A2 (PI6)
/MCU/MCU_LED1: R41.1, U5.A3 (PI5)
/MCU/MCU_LED2: R42.1, U5.A4 (PI4)
/MCU/MCU_LED3: R43.1, U5.A5 (PB5)
/MCU/MCU_PMOD_DQ0: J24.1 (D0), U5.H2 (PI13)
/MCU/MCU_PMOD_DQ1: J24.2 (D1), U5.G3 (PF1)
/MCU/MCU_PMOD_DQ2: J24.3 (D2), U5.E2 (PI9)
/MCU/MCU_PMOD_DQ3: J24.4 (D3), U5.E3 (PC13)
/MCU/MCU_PMOD_DQ4: J24.7 (D4), U5.H1 (PI12)
/MCU/MCU_PMOD_DQ5: J24.8 (D5), U5.G1 (PF2)
/MCU/MCU_PMOD_DQ6: J24.9 (D6), U5.F3 (PI10)
/MCU/MCU_PMOD_DQ7: J24.10 (D7), U5.H3 (PI14)
/MCU/MCU_RST_N: C59.2, J4.10 (~RST), R26.2, R27.2, U5.K1 (NRST); also elsewhere on the board
/MCU/MCU_TRIG: TP12.1, U5.D6 (PG15)
/MCU/PAM3_TX_N: R68.1, U4.R19 (IO_L5N_T0_D07_14)
/MCU/PAM3_TX_P: R67.1, U4.P19 (IO_L5P_T0_D06_14)
/MCU/QSPI_CS_N: R35.1, R46.2, U8.1 (CS#)
/MCU/QSPI_DQ0: R30.1, R48.1
/MCU/QSPI_DQ1: R31.1, R49.2
/MCU/QSPI_DQ2: R32.1, R44.2, R50.2
/MCU/QSPI_DQ3: R33.1, R45.2, R47.1
/MCU/TRACECLK: J4.12 (TRACECLK), U5.C3 (TRACECLK)
/MCU/TRACED0: J4.14 (TRACED0), U5.D9 (TRACED0)
/MCU/TRACED1: J4.16 (TRACED1), U5.D8 (TRACED1)
/MCU/TRACED2: J4.18 (TRACED2), U5.D12 (TRACED2)
/MCU/TRACED3: J4.20 (TRACED3), U5.C12 (TRACED3)
/MCU/UART_CTS_N: U5.U5 (UART4_CTS); also elsewhere on the board
/MCU/UART_RTS_N: U5.U15 (UART4_RTS); also elsewhere on the board
/MCU/UART_RX: U5.N4 (UART4_RX); also elsewhere on the board
/MCU/UART_TX: U5.N5 (UART4_TX); also elsewhere on the board
/MCU/VCORE: C62.1, C66.1, TP9.1 (In), U5.A7 (VCAP), U5.D17 (VCAP), U5.U11 (VCAP)
/Power Supply/SUPER_I2C_SCL: U5.D5 (I2C1_SCL); also elsewhere on the board
/Power Supply/SUPER_I2C_SDA: U5.D4 (I2C1_SDA); also elsewhere on the board
unnamed: D4.2 (A), R39.2
unnamed: D5.2 (A), R41.2
unnamed: D6.2 (A), R42.2
unnamed: D7.2 (A), R43.2
unnamed: J28.1 (In), R67.2
unnamed: J29.1 (In), R68.2
unnamed: R31.2, U4.R22 (IO_L1N_T0_D01_DIN_14)
unnamed: R30.2, U4.P22 (IO_L1P_T0_D00_MOSI_14)
unnamed: R33.2, U4.R21 (IO_L2N_T0_D03_14)
unnamed: R32.2, U4.P21 (IO_L2P_T0_D02_14)
unnamed: R34.2, U4.U22 (IO_L3P_T0_DQS_PUDC_B_14)
unnamed: R35.2, U4.T19 (IO_L6P_T0_FCS_B_14)
unnamed: R38.2, U5.C6 (JTDO)
unnamed: R28.2, U6.3 (CLK)
unnamed: R29.2, U7.3 (CLK)
unnamed: R48.2, U8.5 (DI/IO0)
unnamed: R49.1, U8.2 (DO/IO1)
unnamed: R47.2, U8.7 (HOLD#/IO3)
unnamed: R50.1, U8.3 (WP#/IO2)

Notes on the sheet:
TRACECLK / A23 unavoidably conflict So limit to 2^22 words (2^23 = 0x80_0000 bytes) of APB address space
VDDLDO
VCAP
VDD33USB
VDD
MCU VDDA decoupling
